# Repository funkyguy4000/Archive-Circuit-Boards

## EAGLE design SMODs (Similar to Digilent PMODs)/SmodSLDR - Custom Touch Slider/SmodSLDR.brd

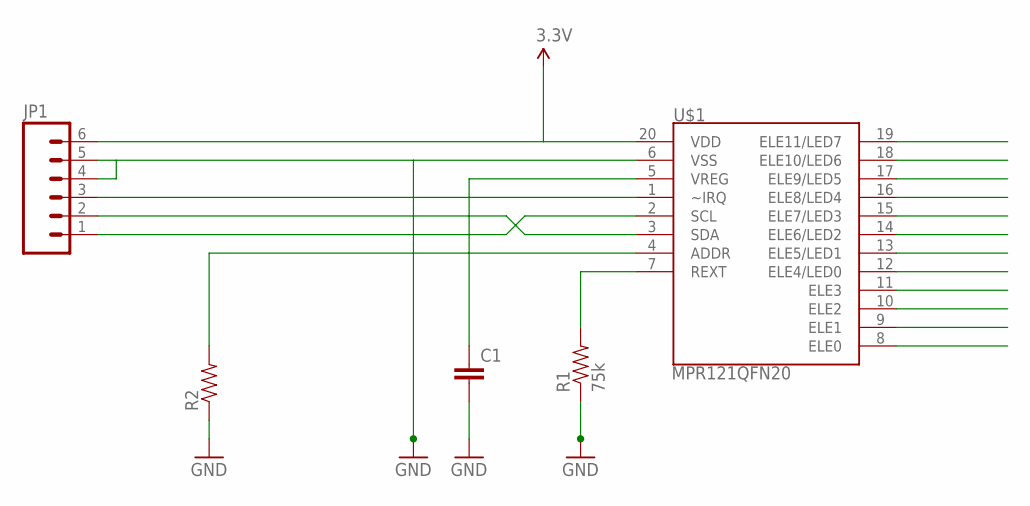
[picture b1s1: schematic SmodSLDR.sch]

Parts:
C1: CAP0603-CAP; 0603-CAP
JP1: M06SIP; 1X06
R1: 75k; 0603-RES
R2: RESISTOR0603-RES; 0603-RES
U$1: MPR121QFN20; QFN-20-0.4MM

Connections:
9: U$1.16 (ELE8/LED4)
ADDR: R2.2, U$1.4 (ADDR)
GND: C1.2, JP1.4, JP1.5, R1.1, R2.1, U$1.6 (VSS)
REXT: R1.2, U$1.7 (REXT)
SCL: JP1.1, U$1.2 (SCL)
SDA: JP1.2, U$1.3 (SDA)
VCC: JP1.6, U$1.20 (VDD)
VREG: C1.1, U$1.5 (VREG)
~IRQ: JP1.3, U$1.1 (~IRQ)

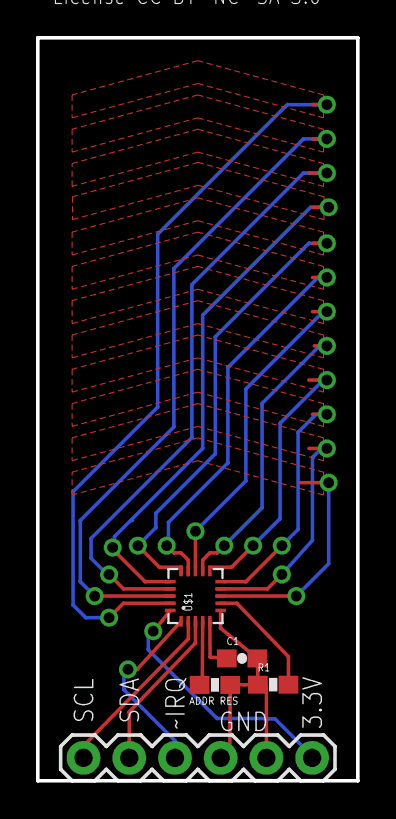
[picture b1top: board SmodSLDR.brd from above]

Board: 2 copper layers, 17.8 x 41.3 mm, 5 parts (0 on the bottom side), 8 nets.

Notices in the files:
SMODs (Similar to Digilent PMODs)/SmodSLDR - Custom Touch Slider/SmodSLDR.brd:
License CC BY-NC-SA 3.0
parts and their libraries:
SparkFun-Sensors: Licensing: CC v3.0 Share-Alike You are welcome to use this library for commercial purposes.
